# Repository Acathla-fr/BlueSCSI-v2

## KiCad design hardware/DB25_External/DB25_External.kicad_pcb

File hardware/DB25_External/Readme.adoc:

# DB25 External BlueSCSI

This is a forked and modified BlueSCSI DB25 External PCB.

It's fully compatible with the original software.

The goal was first to make a PCB anyone can solder at home.

The modifications are :

 * The DB25 connector is mounted in the middle side of the PCB
 
image::Pictures/DB25_External_3D.png[link=https://github.com/Acathla-fr/BlueSCSI-v2/blob/main/hardware/DB25_External/Pictures/DB25_External_3D.png, 400]

 * The pico is soldered under the board with no component in between
 * All passive components are 0805 handsolderable, only a few resistors are under the board
 * New microSD card connector, with sping
 * Almost every component is available on mouser or digikey if you want to assemble it yourself

For the first batch of 9 circuits, the PCBs were made by AISLER (Germany) 
and assembled with a voltera V-One for the solder paste dispensing, 
a small pick&place machine (Neoden YY1) for most passives and the rest by hand.

Reflow was done on a hot plate.

image::Pictures/DB25_External_back.png[link=https://github.com/Acathla-fr/BlueSCSI-v2/blob/main/hardware/DB25_External/Pictures/DB25_External_back.png, 400]

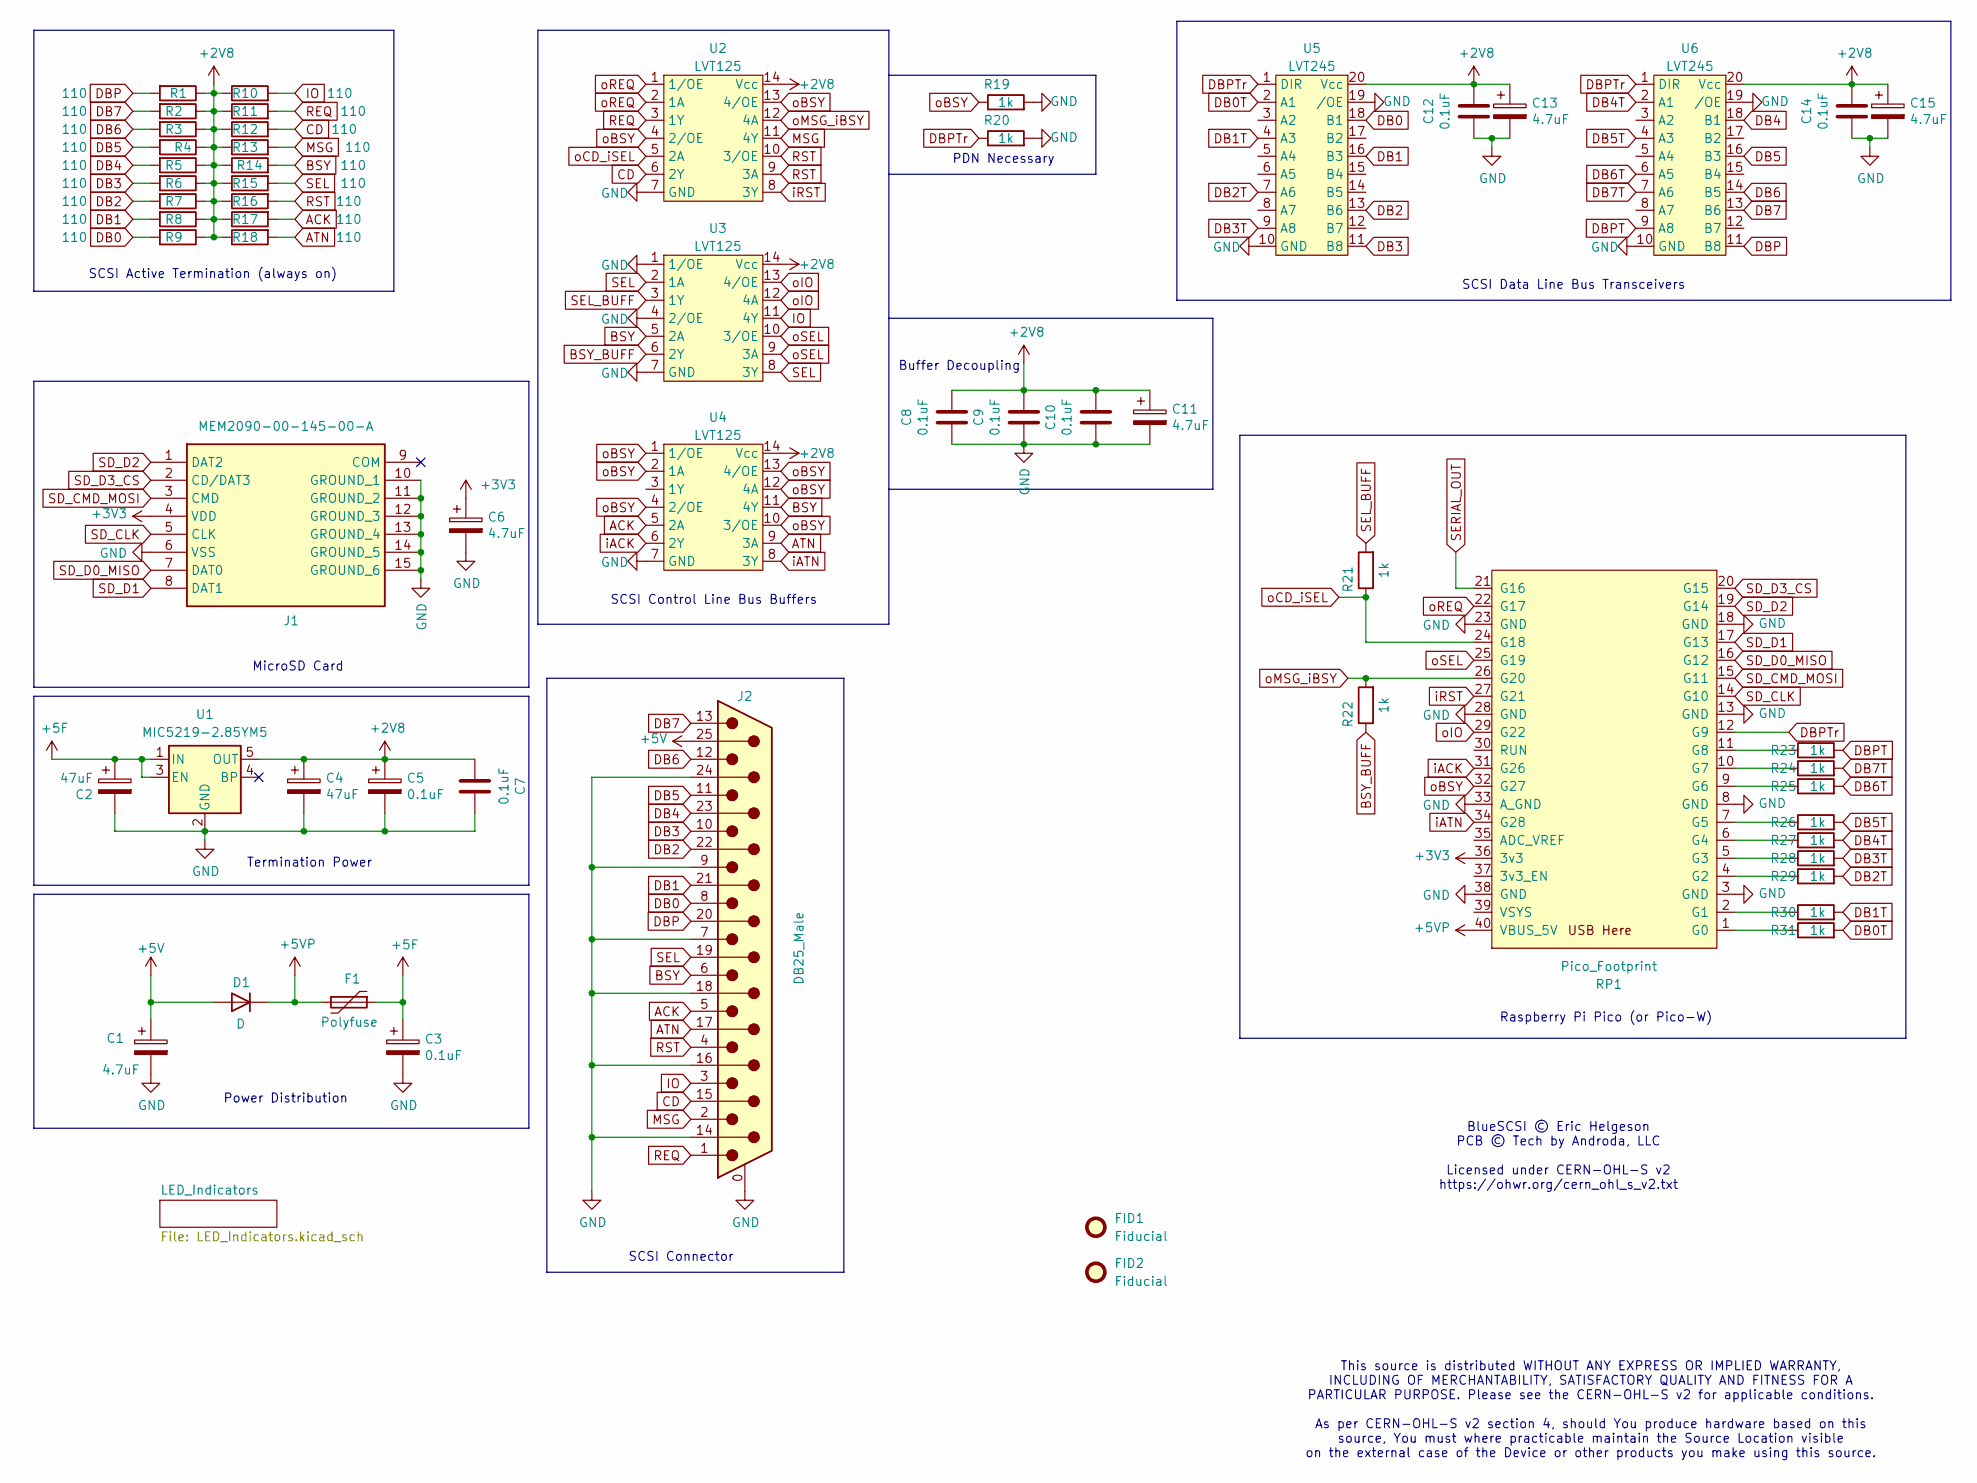
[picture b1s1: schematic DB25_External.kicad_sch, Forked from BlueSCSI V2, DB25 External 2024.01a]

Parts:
C1, C6, C11, C13, C15: 4.7uF; C_0805_2012Metric_Pad1.18x1.45mm_HandSolder
C2, C4: 47uF; C_1206_3216Metric_Pad1.33x1.80mm_HandSolder
C3, C5, C7, C8, C9, C10, C12, C14: 0.1uF; C_0805_2012Metric_Pad1.18x1.45mm_HandSolder
D1: D; D_SMA_Handsoldering
F1: Polyfuse; Fuse_0805_2012Metric_Pad1.15x1.40mm_HandSolder
FID1, FID2: Fiducial; Fiducial_0.5mm_Mask1.5mm
J1: MEM2090-00-145-00-A; MEM20900014500A; Manufacturer_Part_Number MEM2090-00-145-00-A; Mouser Part Number 640-MEM20900014500A
J2: DB25_Male; DSUB-25_Male_Horizontal_middle_mount
R1, R2, R3, R4, R5, R6, R7, R8, R9, R10, R11, R12, R13, R14, R15, R16, R17, R18: 110; R_0805_2012Metric_Pad1.20x1.40mm_HandSolder
R19, R20, R21, R22, R23, R24, R25, R26, R27, R28, R29, R30, R31: 1k; R_0805_2012Metric_Pad1.20x1.40mm_HandSolder
RP1: Pico_Footprint; BluePillModule
U1: MIC5219-2.85YM5; SOT-23-5
U2, U3, U4: LVT125; TSSOP-14_4.4x5mm_P0.65mm
U5, U6: LVT245; TSSOP-20_4.4x6.5mm_P0.65mm

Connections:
+2V8: C4.1, C5.1, C7.1, C8.2, C9.2, C10.2, C11.1, C12.1, C13.1, C14.1, C15.1, R1.1, R2.1, R3.1, R4.1, R5.1, R6.1, R7.1, R8.1, R9.1, R10.1, R11.1, R12.1, R13.1, R14.1, R15.1, R16.1, R17.1, R18.1, U1.5 (OUT), U2.14 (Vcc), U3.14 (Vcc), U4.14 (Vcc), U5.20 (Vcc), U6.20 (Vcc)
+3V3: C6.1, J1.4 (VDD), RP1.36 (3v3); also elsewhere on the board
+5F: C2.1, C3.1, F1.1, U1.1 (IN), U1.3 (EN); also elsewhere on the board
+5V: C1.1, D1.2 (A), J2.25
+5VP: D1.1 (K), F1.2, RP1.40 (VBUS_5V)
ACK: J2.5, R17.2, U4.5 (2A)
ATN: J2.17, R18.2, U4.9 (3A)
BSY: J2.6, R14.2, U3.5 (2A), U4.11 (4Y)
BSY_BUFF: R22.1, U3.6 (2Y)
CD: J2.15, R12.2, U2.6 (2Y)
DB0: J2.8, R9.2, U5.18 (B1)
DB0T: R31.2, U5.2 (A1)
DB1: J2.21, R8.2, U5.16 (B3)
DB1T: R30.2, U5.4 (A3)
DB2: J2.22, R7.2, U5.13 (B6)
DB2T: R29.2, U5.7 (A6)
DB3: J2.10, R6.2, U5.11 (B8)
DB3T: R28.2, U5.9 (A8)
DB4: J2.23, R5.2, U6.18 (B1)
DB4T: R27.2, U6.2 (A1)
DB5: J2.11, R4.2, U6.16 (B3)
DB5T: R26.2, U6.4 (A3)
DB6: J2.12, R3.2, U6.14 (B5)
DB6T: R25.2, U6.6 (A5)
DB7: J2.13, R2.2, U6.13 (B6)
DB7T: R24.2, U6.7 (A6)
DBP: J2.20, R1.2, U6.11 (B8)
DBPT: R23.2, U6.9 (A8)
DBPTr: R20.1, RP1.12 (G9), U5.1 (DIR), U6.1 (DIR)
GND: C1.2, C2.2, C3.2, C4.2, C5.2, C6.2, C7.2, C8.1, C9.1, C10.1, C11.2, C12.2, C13.2, C14.2, C15.2, J1.6 (VSS), J1.10 (GROUND_1), J1.11 (GROUND_2), J1.12 (GROUND_3), J1.13 (GROUND_4), J1.14 (GROUND_5), J1.15 (GROUND_6), J2.0 (PAD), J2.7, J2.9, J2.14, J2.16, J2.18, J2.24, R19.2, R20.2, RP1.3 (GND), RP1.8 (GND), RP1.13 (GND), RP1.18 (GND), RP1.23 (GND), RP1.28 (GND), RP1.33 (A_GND), RP1.38 (GND), U1.2 (GND), U2.7 (GND), U3.1 (1/OE), U3.4 (2/OE), U3.7 (GND), U4.7 (GND), U5.10 (GND), U5.19 (/OE), U6.10 (GND), U6.19 (/OE); also elsewhere on the board
IO: J2.3, R10.2, U3.11 (4Y)
MSG: J2.2, R13.2, U2.11 (4Y)
unnamed: R31.1, RP1.1 (G0)
unnamed: R30.1, RP1.2 (G1)
unnamed: R29.1, RP1.4 (G2)
unnamed: R28.1, RP1.5 (G3)
unnamed: R27.1, RP1.6 (G4)
unnamed: R26.1, RP1.7 (G5)
unnamed: R25.1, RP1.9 (G6)
unnamed: R24.1, RP1.10 (G7)
unnamed: R23.1, RP1.11 (G8)
REQ: J2.1, R11.2, U2.3 (1Y)
RST: J2.4, R16.2, U2.9 (3A), U2.10 (3/OE)
SD_CLK: J1.5 (CLK), RP1.14 (G10)
SD_CMD_MOSI: J1.3 (CMD), RP1.15 (G11)
SD_D0_MISO: J1.7 (DAT0), RP1.16 (G12)
SD_D1: J1.8 (DAT1), RP1.17 (G13)
SD_D2: J1.1 (DAT2), RP1.19 (G14)
SD_D3_CS: J1.2 (CD/DAT3), RP1.20 (G15)
SEL: J2.19, R15.2, U3.2 (1A), U3.8 (3Y)
SEL_BUFF: R21.2, U3.3 (1Y)
SERIAL_OUT: RP1.21 (G16)
iACK: RP1.31 (G26), U4.6 (2Y)
iATN: RP1.34 (G28), U4.8 (3Y)
iRST: RP1.27 (G21), U2.8 (3Y)
oBSY: R19.1, RP1.32 (G27), U2.4 (2/OE), U2.13 (4/OE), U4.1 (1/OE), U4.2 (1A), U4.4 (2/OE), U4.10 (3/OE), U4.12 (4A), U4.13 (4/OE); also elsewhere on the board
oCD_iSEL: R21.1, RP1.24 (G18), U2.5 (2A)
oIO: RP1.29 (G22), U3.12 (4A), U3.13 (4/OE)
oMSG_iBSY: R22.2, RP1.26 (G20), U2.12 (4A)
oREQ: RP1.22 (G17), U2.1 (1/OE), U2.2 (1A)
oSEL: RP1.25 (G19), U3.9 (3A), U3.10 (3/OE)

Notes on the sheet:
Termination Power
Raspberry Pi Pico (or Pico-W)
MicroSD Card
BlueSCSI © Eric Helgeson PCB © Tech by Androda, LLC Licensed under CERN-OHL-S v2 https://ohwr.org/cern_ohl_s_v2.txt
Power Distribution
SCSI Connector
SCSI Data Line Bus Transceivers
SCSI Control Line Bus Buffers
PDN Necessary
This source is distributed WITHOUT ANY EXPRESS OR IMPLIED WARRANTY, INCLUDING OF MERCHANTABILITY, SATISFACTORY QUALITY AND FITNESS FOR A PARTICULAR PURPOSE. Please see the CERN-OHL-S v2 for applicable conditions. As per CERN-OHL-S v2 section 4, should You produce hardware based on this source, You 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
SCSI Active Termination (always on)
Buffer Decoupling

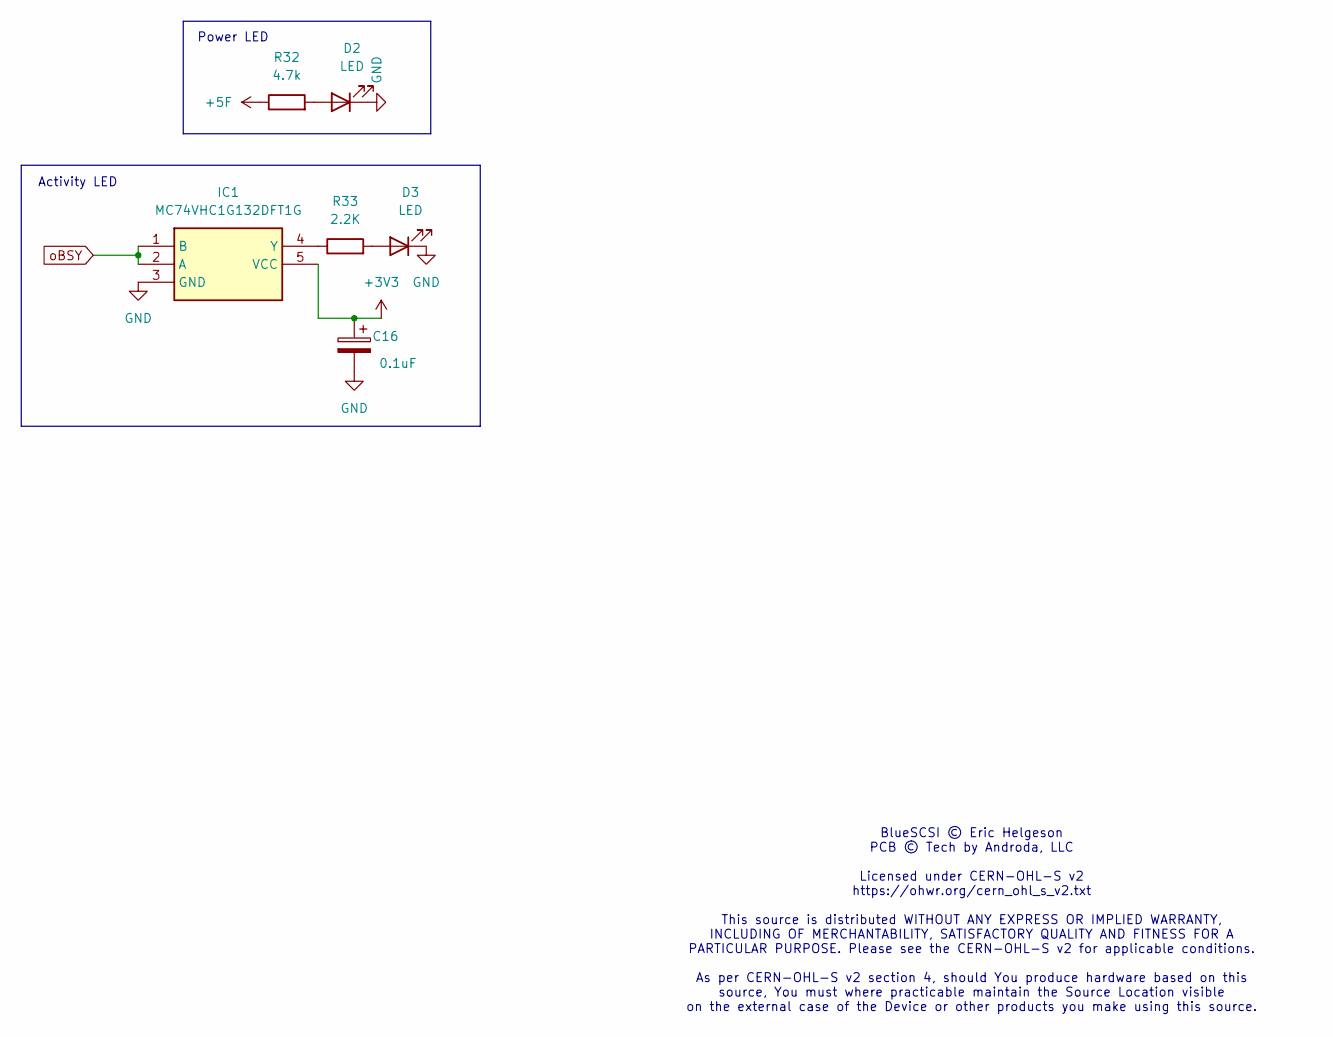
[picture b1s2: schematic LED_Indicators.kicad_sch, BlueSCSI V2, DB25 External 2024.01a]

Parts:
C16: 0.1uF; C_0805_2012Metric_Pad1.18x1.45mm_HandSolder
D2, D3: LED; LED_0805_2012Metric_Pad1.15x1.40mm_HandSolder
IC1: MC74VHC1G132DFT1G; SOT65P210X110-5N; Manufacturer_Part_Number MC74VHC1G132DFT1G; Mouser Part Number 863-C74VHC1G132DFT1G
R32: 4.7k; R_0805_2012Metric_Pad1.20x1.40mm_HandSolder
R33: 2.2K; R_0805_2012Metric_Pad1.20x1.40mm_HandSolder

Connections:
+3V3: C16.1, IC1.5 (VCC); also elsewhere on the board
+5F: R32.1; also elsewhere on the board
GND: C16.2, D2.1 (K), D3.1 (K), IC1.3 (GND); also elsewhere on the board
unnamed: D2.2 (A), R32.2
unnamed: D3.2 (A), R33.2
unnamed: IC1.4 (Y), R33.1
oBSY: IC1.1 (B), IC1.2 (A); also elsewhere on the board

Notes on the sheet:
Power LED
BlueSCSI © Eric Helgeson PCB © Tech by Androda, LLC Licensed under CERN-OHL-S v2 https://ohwr.org/cern_ohl_s_v2.txt This source is distributed WITHOUT ANY EXPRESS OR IMPLIED WARRANTY, INCLUDING OF MERCHANTABILITY, SATISFACTORY QUALITY AND FITNESS FOR A PARTICULAR PURPOSE. Please see the CERN-OHL-S 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
Activity LED

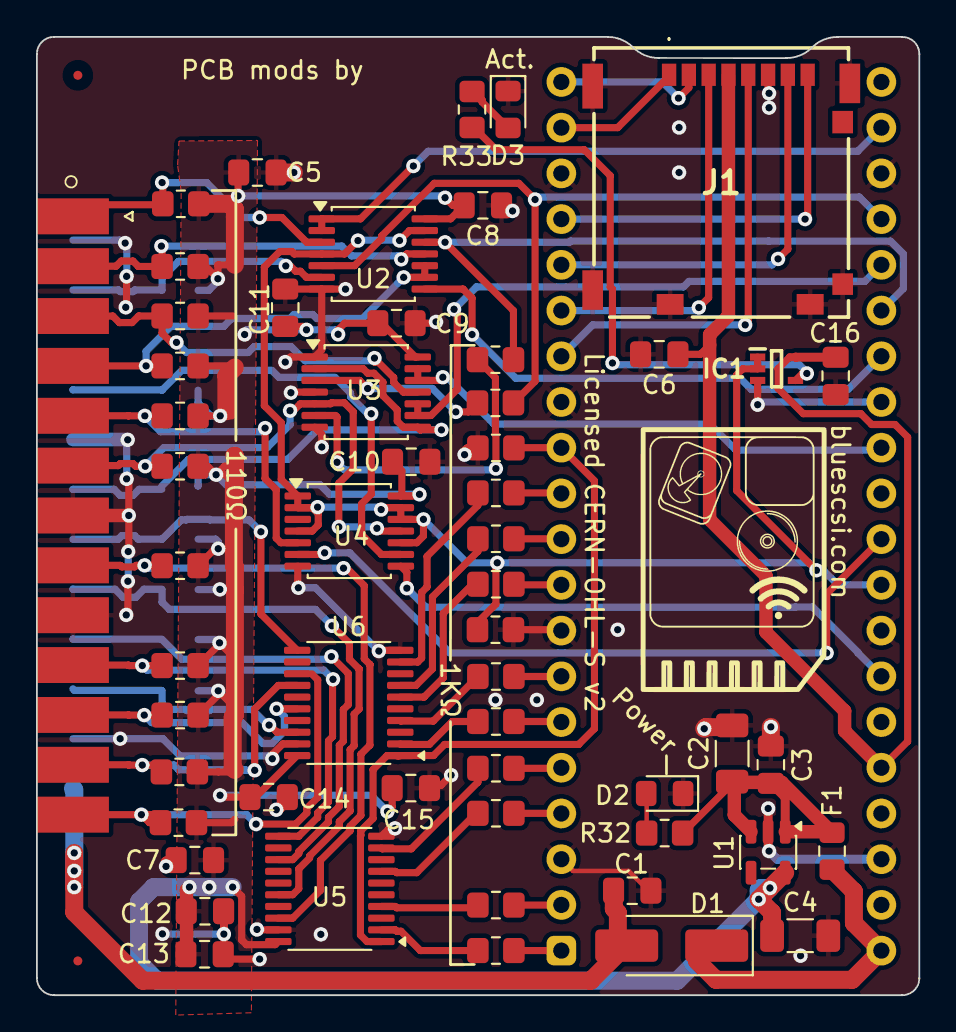
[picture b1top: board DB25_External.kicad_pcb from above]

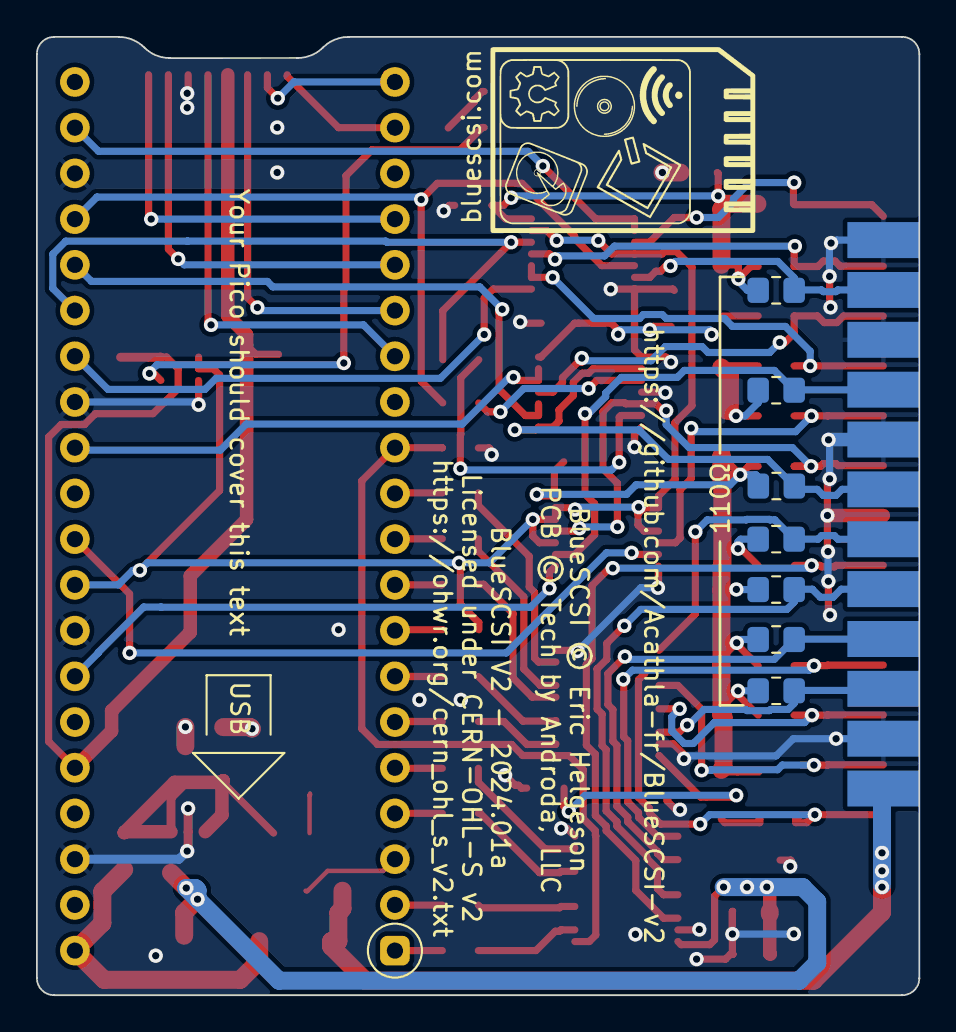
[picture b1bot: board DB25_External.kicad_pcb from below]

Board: 2 copper layers, 49.0 x 53.2 mm, 65 parts (8 on the bottom side), 63 nets.

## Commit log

2026-01-01 My version sent to Aisler, pico under the PCB
2026-02-05 Via moved out of pad and original (c) text added
2026-02-05 3D View pictures added
2026-02-06 Clean up
2026-02-06 Clean up bis
2026-02-06 Fixed link to pictures in Readme.adoc

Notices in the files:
hardware/DB25_External/DB25_External.kicad_pcb:
Licensed CERN-OHL-S v2
